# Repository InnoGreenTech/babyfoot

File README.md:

# babyfoot
This a babyfoot ambiente, it allow to animate a game of table football with neopixel , matrix led and sound.

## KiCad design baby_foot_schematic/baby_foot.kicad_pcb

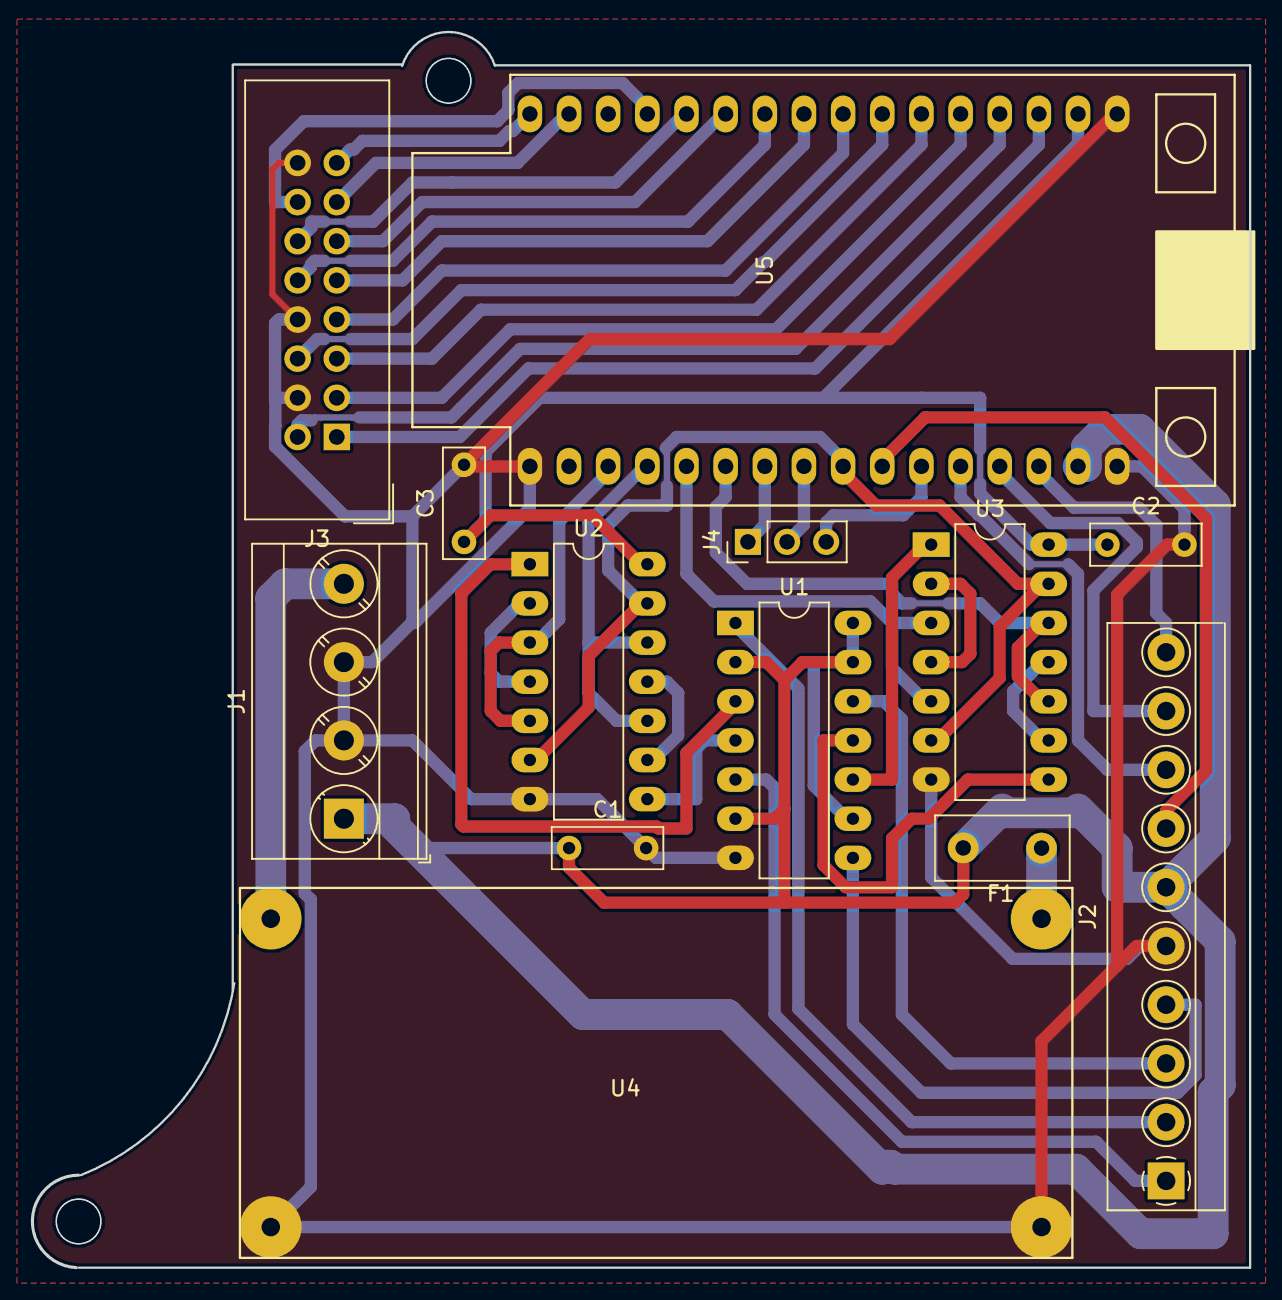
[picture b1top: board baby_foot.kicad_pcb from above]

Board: 2 copper layers, 79.0 x 80.1 mm, 13 parts (0 on the bottom side), 42 nets.

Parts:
C1, C2, C3: C; C_Rect_L7.0mm_W2.5mm_P5.00mm
F1: Fuse; Fuse_Littelfuse_395Series
J1: PW; TerminalBlock_Phoenix_MKDS-3-4-5.08_1x04_P5.08mm_Horizontal
J2: Signal; TerminalBlock_4Ucon_1x10_P3.81mm_Horizontal
J3: Conn_02x08_Odd_Even; IDC-Header_2x08_P2.54mm_Vertical
J4: Touch buttom; PinHeader_1x03_P2.54mm_Vertical
U1, U2, U3: 4011; DIP-14_W7.62mm_LongPads
U4: DCDC_24_5; Board_ADJ_5A
U5: uPesyESP32; uPesy_ESP32_ Wroom

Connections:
+3V3: C2.1, C3.1, U2.14, U3.14, U5.31
+5V: C1.1, F1.2, J1.1, J2.6, U1.2, U1.6, U1.9, U1.13, U1.14, U5.15
A: J3.9, U5.24
B: J3.10, U5.23
B1: J3.3, U5.28
B2: J3.7, U5.25
C: J3.11, U5.22
CLK: J3.13, U5.18
D: J3.12, U5.21
G1: J3.2, U5.29
G2: J3.6, U5.26
GND: C1.2, C2.2, C3.2, J1.2, J1.3, J2.5, J3.4, J3.8, J3.16, U1.7, U2.7, U3.7, U4.2, U4.4, U5.1, U5.16, U5.32
Gam_J1: U2.10, U2.12, U5.4
Gam_J2: U3.10, U3.12, U5.6
Goal_J1: U2.3, U2.5, U5.3
Goal_J2: U3.3, U3.5, U5.5
LAT: J3.14, U5.20
LED_1: J2.7, U5.10
LED_2: J2.8, U5.12
LESS: J4.1, U5.7
MORE: J4.2, U5.8
unnamed: F1.1, U4.3
unnamed: J1.4, U4.1
unnamed: J2.1, U1.5
unnamed: J2.2, U1.1
unnamed: J2.3, U1.12
unnamed: J2.4, U1.8
unnamed: U1.3, U2.1
unnamed: U1.4, U2.8
unnamed: U1.10, U3.1
unnamed: U1.11, U3.8
unnamed: U2.2, U2.4
unnamed: U2.9, U2.11
unnamed: U3.2, U3.4
unnamed: U3.9, U3.11
OE: J3.15, U5.17
OK: J4.3, U5.11
R1: J3.1, U5.30
R2: J3.5, U5.27
RX: J2.9, U5.13
Reset: U2.6, U2.13, U3.6, U3.13, U5.9
TX: J2.10, U5.14

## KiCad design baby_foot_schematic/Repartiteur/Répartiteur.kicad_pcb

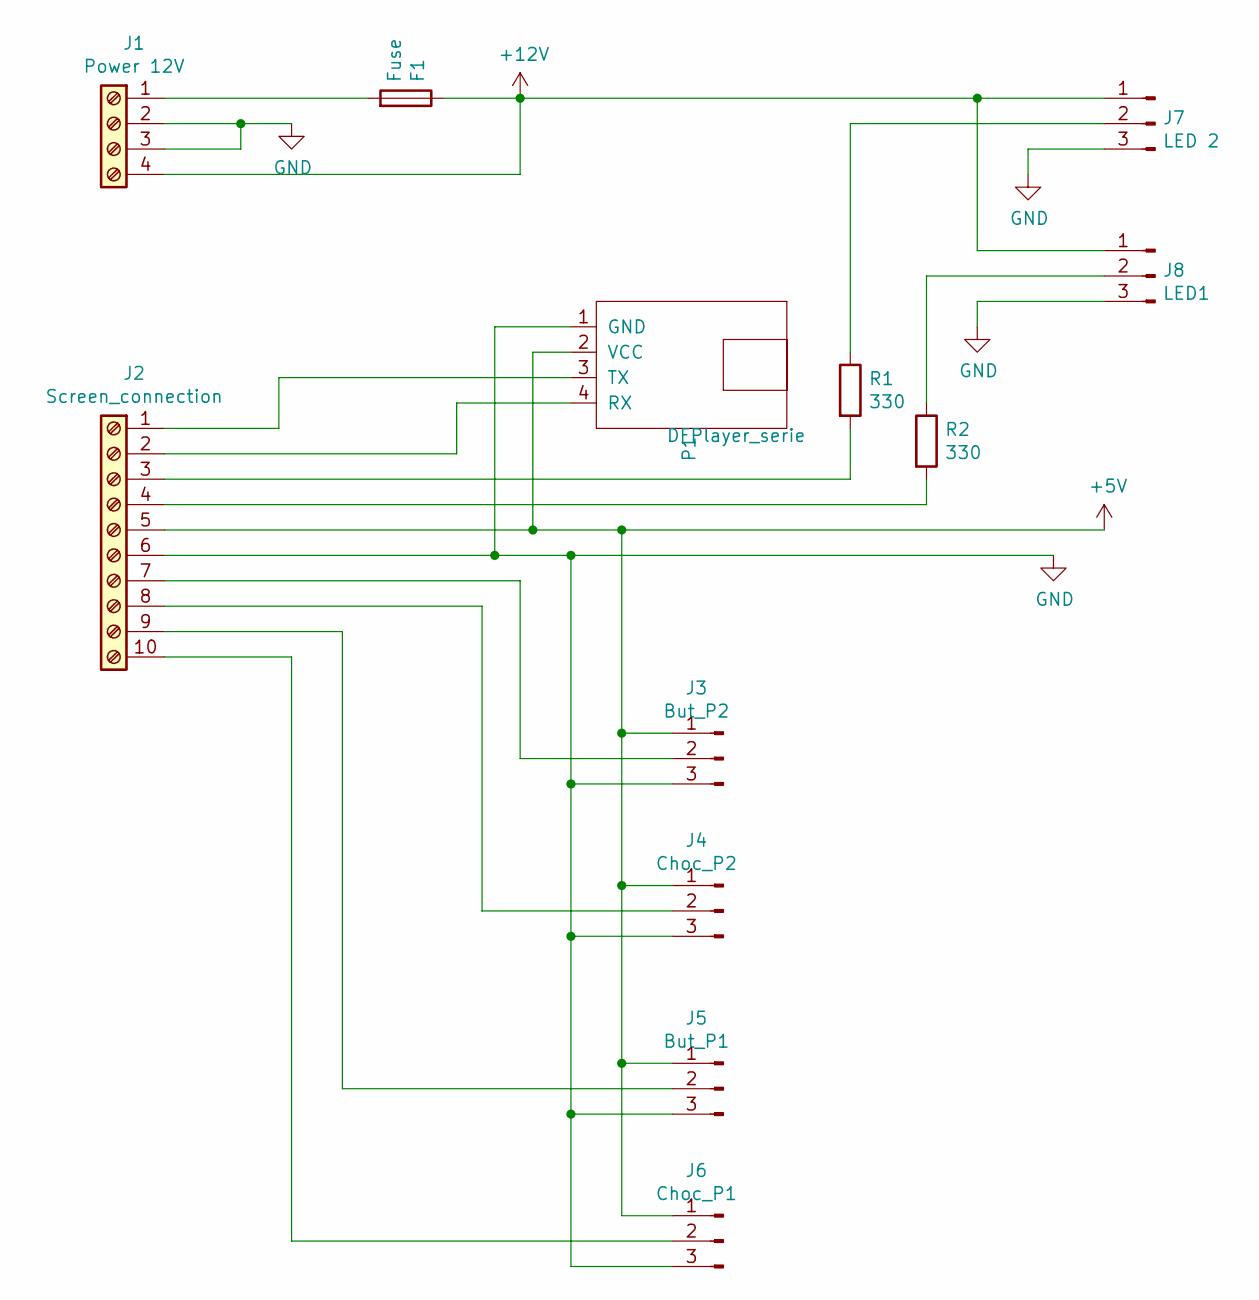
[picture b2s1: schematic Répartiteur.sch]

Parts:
F1: Fuse; Fuseholder_Cylinder-5x20mm_Stelvio-Kontek_PTF78_Horizontal_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
J1: Power 12V; TerminalBlock_MetzConnect_Type101_RT01604HBWC_1x04_P5.08mm_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
J2: Screen_connection; TerminalBlock_4Ucon_1x10_P3.81mm_Horizontal
J3: But_P2; PinHeader_1x03_P2.54mm_Horizontal
J4: Choc_P2; PinHeader_1x03_P2.54mm_Horizontal
J5: But_P1; PinHeader_1x03_P2.54mm_Horizontal
J6: Choc_P1; PinHeader_1x03_P2.54mm_Horizontal
J7: LED 2; PinHeader_1x03_P2.54mm_Horizontal
J8: LED1; PinHeader_1x03_P2.54mm_Horizontal
P1: DFPlayer_serie
R1, R2: 330; R_Axial_DIN0207_L6.3mm_D2.5mm_P10.16mm_Horizontal

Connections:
+5V: J2.5, J3.1, J4.1, J5.1, J6.1, P1.2 (VCC)
+12V: F1.1, J1.4, J7.1, J8.1
GND: J1.2, J1.3, J2.6, J3.3, J4.3, J5.3, J6.3, J7.3, J8.3, P1.1 (GND)
unnamed: F1.2, J1.1
unnamed: J2.1, P1.3 (TX)
unnamed: J2.2, P1.4 (RX)
unnamed: J2.3, R1.2
unnamed: J2.4, R2.2
unnamed: J2.7, J3.2
unnamed: J2.8, J4.2
unnamed: J2.9, J5.2
unnamed: J2.10, J6.2
unnamed: J7.2, R1.1
unnamed: J8.2, R2.1

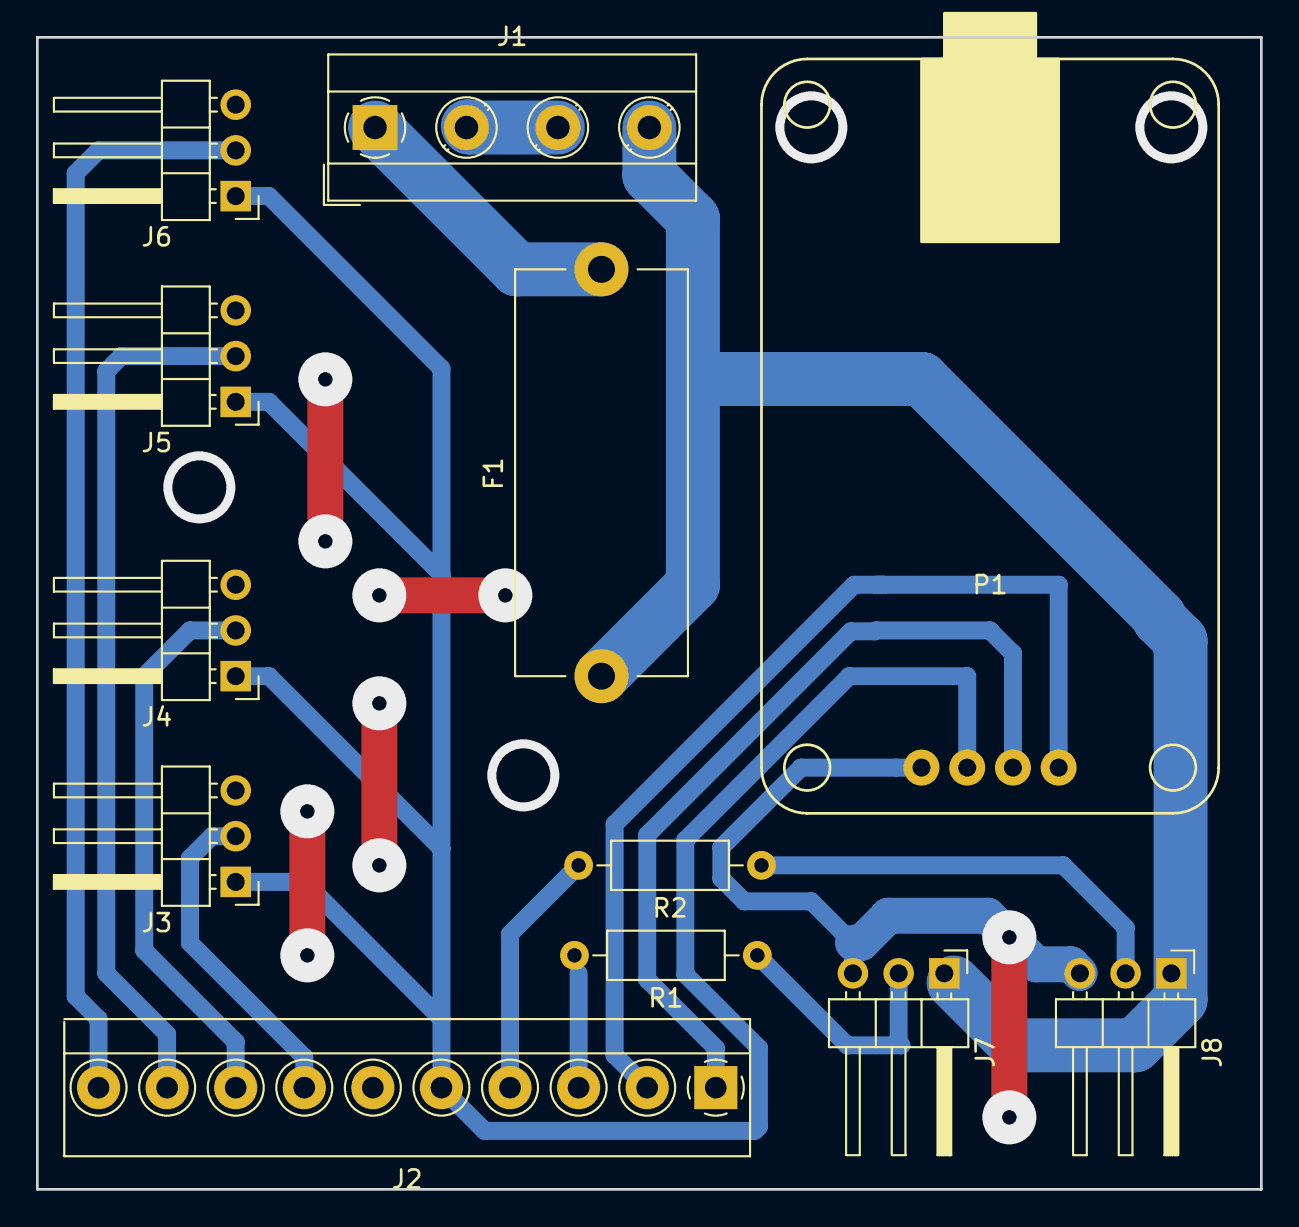
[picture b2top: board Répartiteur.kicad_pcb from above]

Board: 2 copper layers, 68.0 x 64.0 mm, 12 parts (0 on the bottom side), 14 nets.

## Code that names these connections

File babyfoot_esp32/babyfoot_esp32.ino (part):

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//Default connection
//uint8 OE = 23;
//uint8 CLK = 22;
//uint8 LAT = 03;
//uint8 CH_A = 21;
//uint8 CH_B = 19;
//uint8 CH_C = 18;
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volatile unsigned int inputs=0;            // use bit to read input               

#define OK          0
#define LESS        1
#define MORE        2
#define GOAL_P1     3
#define GAMELLE_P1  4
#define GOAL_P2     5
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
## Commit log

2021-04-01 Create LICENSE
2021-04-10 debug touch botom

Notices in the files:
babyfoot_esp32/babyfoot_esp32.ino:
Copyright (C) <2019>  <Fabrice BAUDIN>
This program is free software: you can redistribute it and/or modify
it under the terms of the GNU General Public License as published by
the Free Software Foundation, either version 3 of the License.
